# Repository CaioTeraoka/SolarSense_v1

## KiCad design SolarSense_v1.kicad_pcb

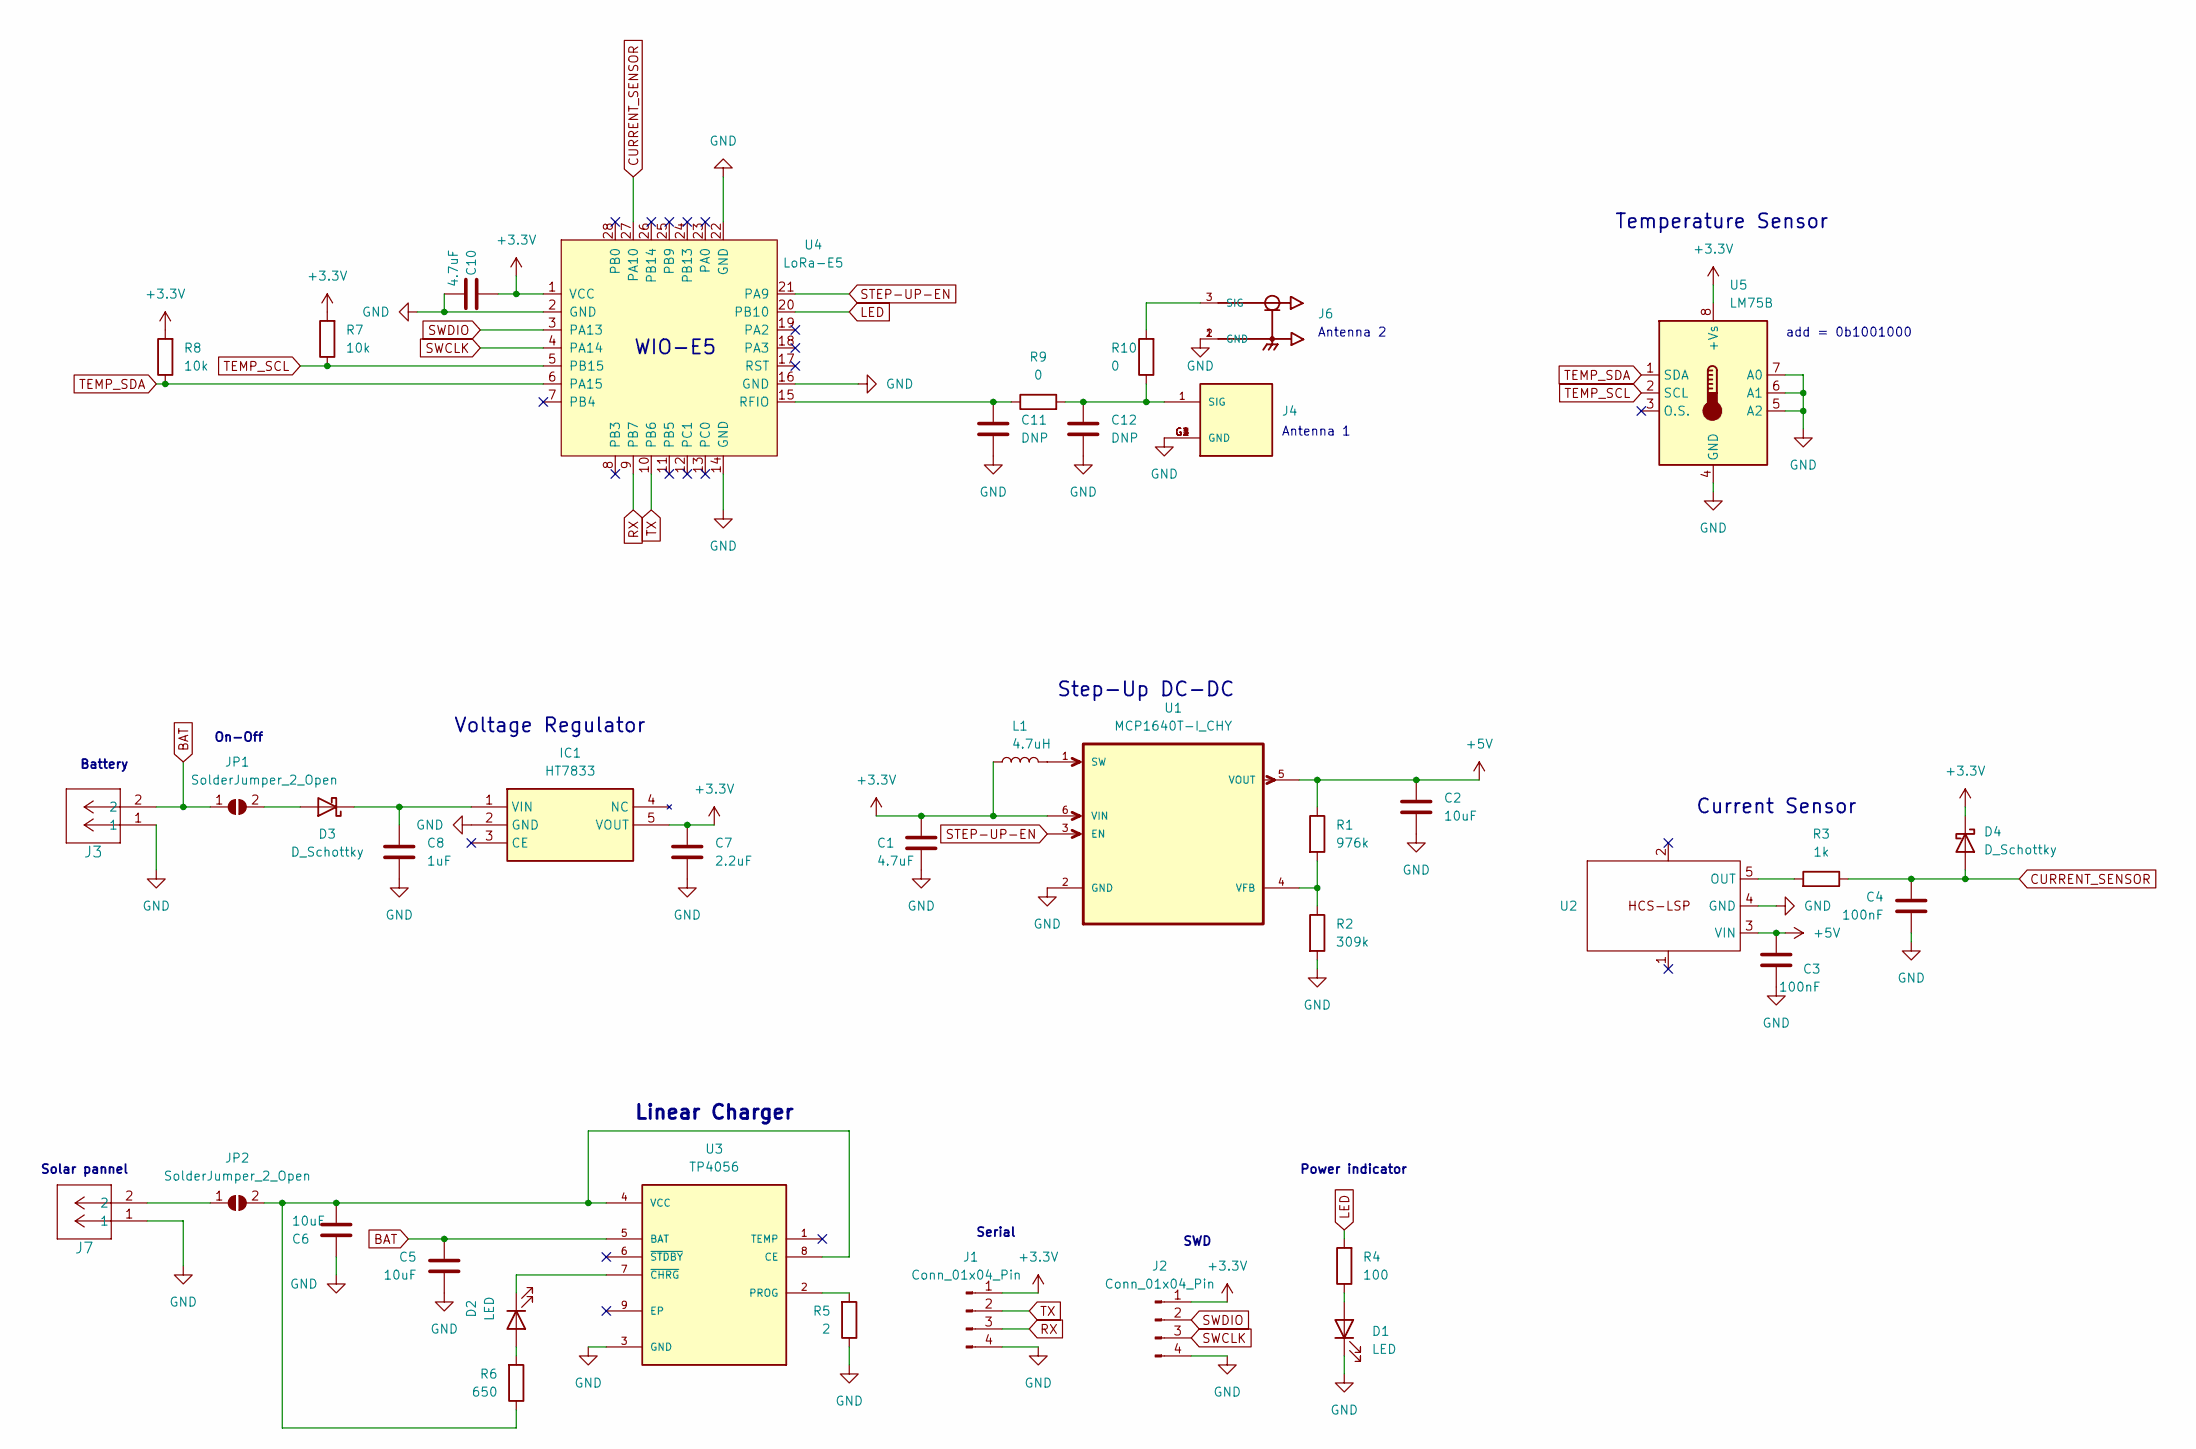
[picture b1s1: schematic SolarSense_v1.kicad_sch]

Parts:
C1, C10: 4.7uF; C_1206_3216Metric; LCSC C967600
C2, C5, C6: 10uF; C_1206_3216Metric; LCSC C5189826
C3, C4: 100nF; C_1206_3216Metric; LCSC C5448901
C7: 2.2uF; C_1206_3216Metric
C8: 1uF; C_1206_3216Metric
C11, C12: DNP; C_0603_1608Metric
D1, D2: LED; LED_1206_3216Metric; LCSC C965825
D3, D4: D_Schottky; D_1206_3216Metric; LCSC C143806
IC1: HT7833; SOT95P280X80-5N; Manufacturer_Part_Number HT7833; LCSC C50936
J1, J2: Conn_01x04_Pin; PinHeader_1x04_P2.54mm_Vertical; LCSC C6332197
J3, J7: KF141R-2.54-2P; CONN_KF141R_CKE
J4: BWSMA-KE-P001; BATWIRELESS_BWSMA-KE-P001; PARTREV A; LCSC C496550
J6: U.FL-R-SMT_01_; HRS_U.FL-R-SMT_01_; LCSC C434808
JP1, JP2: SolderJumper_2_Open; SolderJumper-2_P1.3mm_Open_RoundedPad1.0x1.5mm
L1: 4.7uH; L_1206_3216Metric; LCSC C2983018
R1: 976k; R_1206_3216Metric; LCSC C368330
R2: 309k; R_1206_3216Metric; LCSC C3013252
R3: 1k; R_1206_3216Metric; LCSC C2907440
R4: 100; R_1206_3216Metric; LCSC C3017992
R5: 2; R_1206_3216Metric; LCSC C2907468
R6: 650; R_1206_3216Metric; LCSC C2907528
R7, R8: 10k; R_1206_3216Metric; LCSC C3017992
R9, R10: 0; R_0603_1608Metric; LCSC C21189
U1: MCP1640T-I_CHY; SOT95P270X145-6N; MPN MCP1640T-I/CHY; LCSC C478087
U2: HCS-LSP
U3: TP4056; SOP127P600X175-9N; LCSC C725790
U4: LoRa-E5
U5: LM75B; SOP65P490X110-8N; LCSC C2837470

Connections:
+3.3V: C1.1, C7.1, C10.1, D4.1 (K), IC1.5 (VOUT), J1.1, J2.1, L1.1, R7.2, R8.2, U1.6 (VIN), U4.1 (VCC), U5.8 (+Vs)
+5V: C2.1, C3.1, R1.1, U1.5 (VOUT), U2.3 (VIN)
BAT: C5.1, J3.2, JP1.1 (A), U3.5 (BAT)
CURRENT_SENSOR: C4.1, D4.2 (A), R3.1, U4.27 (PA10)
GND: C1.2, C2.2, C3.2, C4.2, C5.2, C6.2, C7.2, C8.2, C10.2, C11.2, C12.2, D1.1 (K), IC1.2 (GND), J1.4, J2.4, J3.1, J4.G1 (GND), J4.G2 (GND), J4.G3 (GND), J4.G4 (GND), J6.1 (GND), J6.2 (GND), J7.1, R2.2, R5.1, U1.2 (GND), U2.4 (GND), U3.3 (GND), U4.2 (GND), U4.14 (GND), U4.16 (GND), U4.22 (GND), U5.4 (GND), U5.5 (A2), U5.6 (A1), U5.7 (A0)
LED: R4.2, U4.20 (PB10)
unnamed: D1.2 (A), R4.1
unnamed: D2.2 (A), R6.2
unnamed: D2.1 (K), U3.7 (~CHRG)
unnamed: D3.2 (A), JP1.2 (B)
unnamed: C8.1, D3.1 (K), IC1.1 (VIN)
unnamed: C12.1, J4.1 (SIG), R9.2, R10.1
unnamed: J6.3 (SIG), R10.2
unnamed: J7.2, JP2.1 (A)
unnamed: C6.1, JP2.2 (B), R6.1, U3.4 (VCC), U3.8 (CE)
unnamed: L1.2, U1.1 (SW)
unnamed: R1.2, R2.1, U1.4 (VFB)
unnamed: R3.2, U2.5 (OUT)
unnamed: R5.2, U3.2 (PROG)
unnamed: C11.1, R9.1, U4.15 (RFIO)
RX: J1.3, U4.9 (PB7)
STEP-UP-EN: U1.3 (EN), U4.21 (PA9)
SWCLK: J2.3, U4.4 (PA14)
SWDIO: J2.2, U4.3 (PA13)
TEMP_SCL: R7.1, U4.5 (PB15), U5.2 (SCL)
TEMP_SDA: R8.1, U4.6 (PA15), U5.1 (SDA)
TX: J1.2, U4.10 (PB6)

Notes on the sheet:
Power indicator
On-Off
Temperature Sensor
add = 0b1001000
Step-Up DC-DC
Antenna 1
WIO-E5
Solar pannel
SWD
Antenna 2
Current Sensor
Serial
Battery
Linear Charger
Voltage Regulator

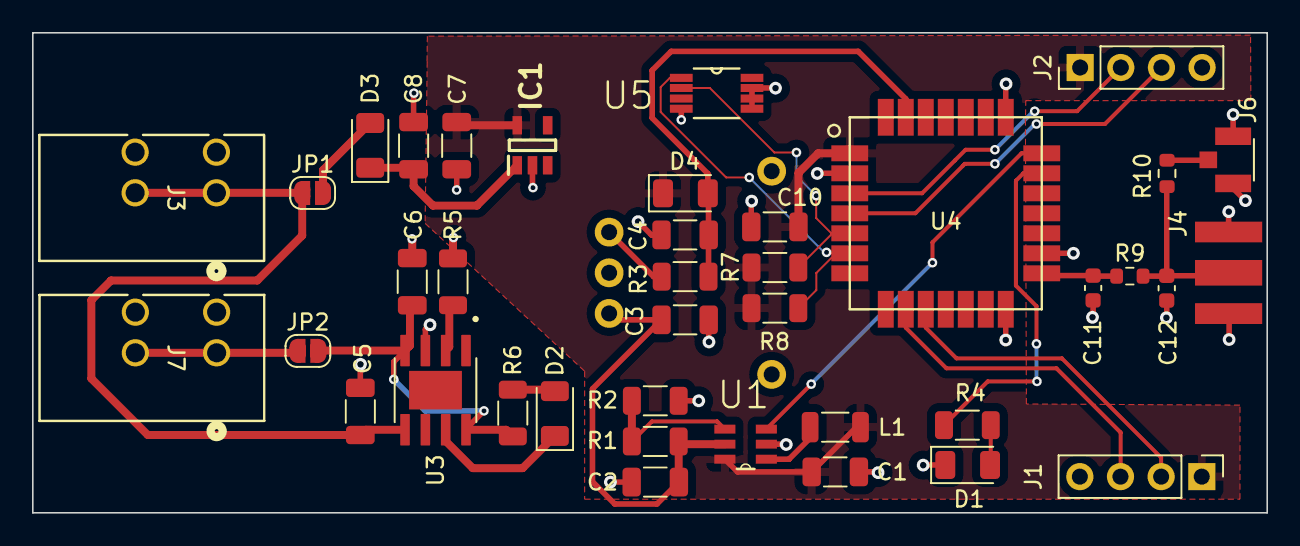
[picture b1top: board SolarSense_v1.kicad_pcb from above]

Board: 2 copper layers, 77.2 x 30.0 mm, 40 parts (1 on the bottom side), 27 nets.

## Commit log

2024-03-12 Schematic done
2024-05-06 First routing
